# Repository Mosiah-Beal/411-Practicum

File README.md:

# A weather monitor placed near a window
Portland State University Team 4 Practicum Project
Mosiah Beal,	Joshua Dworning,	Andy Nguyen,	Joel Utecht,	Casey McGuire

Uses GNU v3 GENERAL PUBLIC LICENSE

Monitors inputs from DHTxx and Rain sensors, with adjustable tolerances.
Supports Serial communication and has dedicated display/keypad to provide a user interface.
Can be integrated into smart home networks through use of Sinric Pro
Features status leds and piezo buzzer as redundant systems in advent of device failure

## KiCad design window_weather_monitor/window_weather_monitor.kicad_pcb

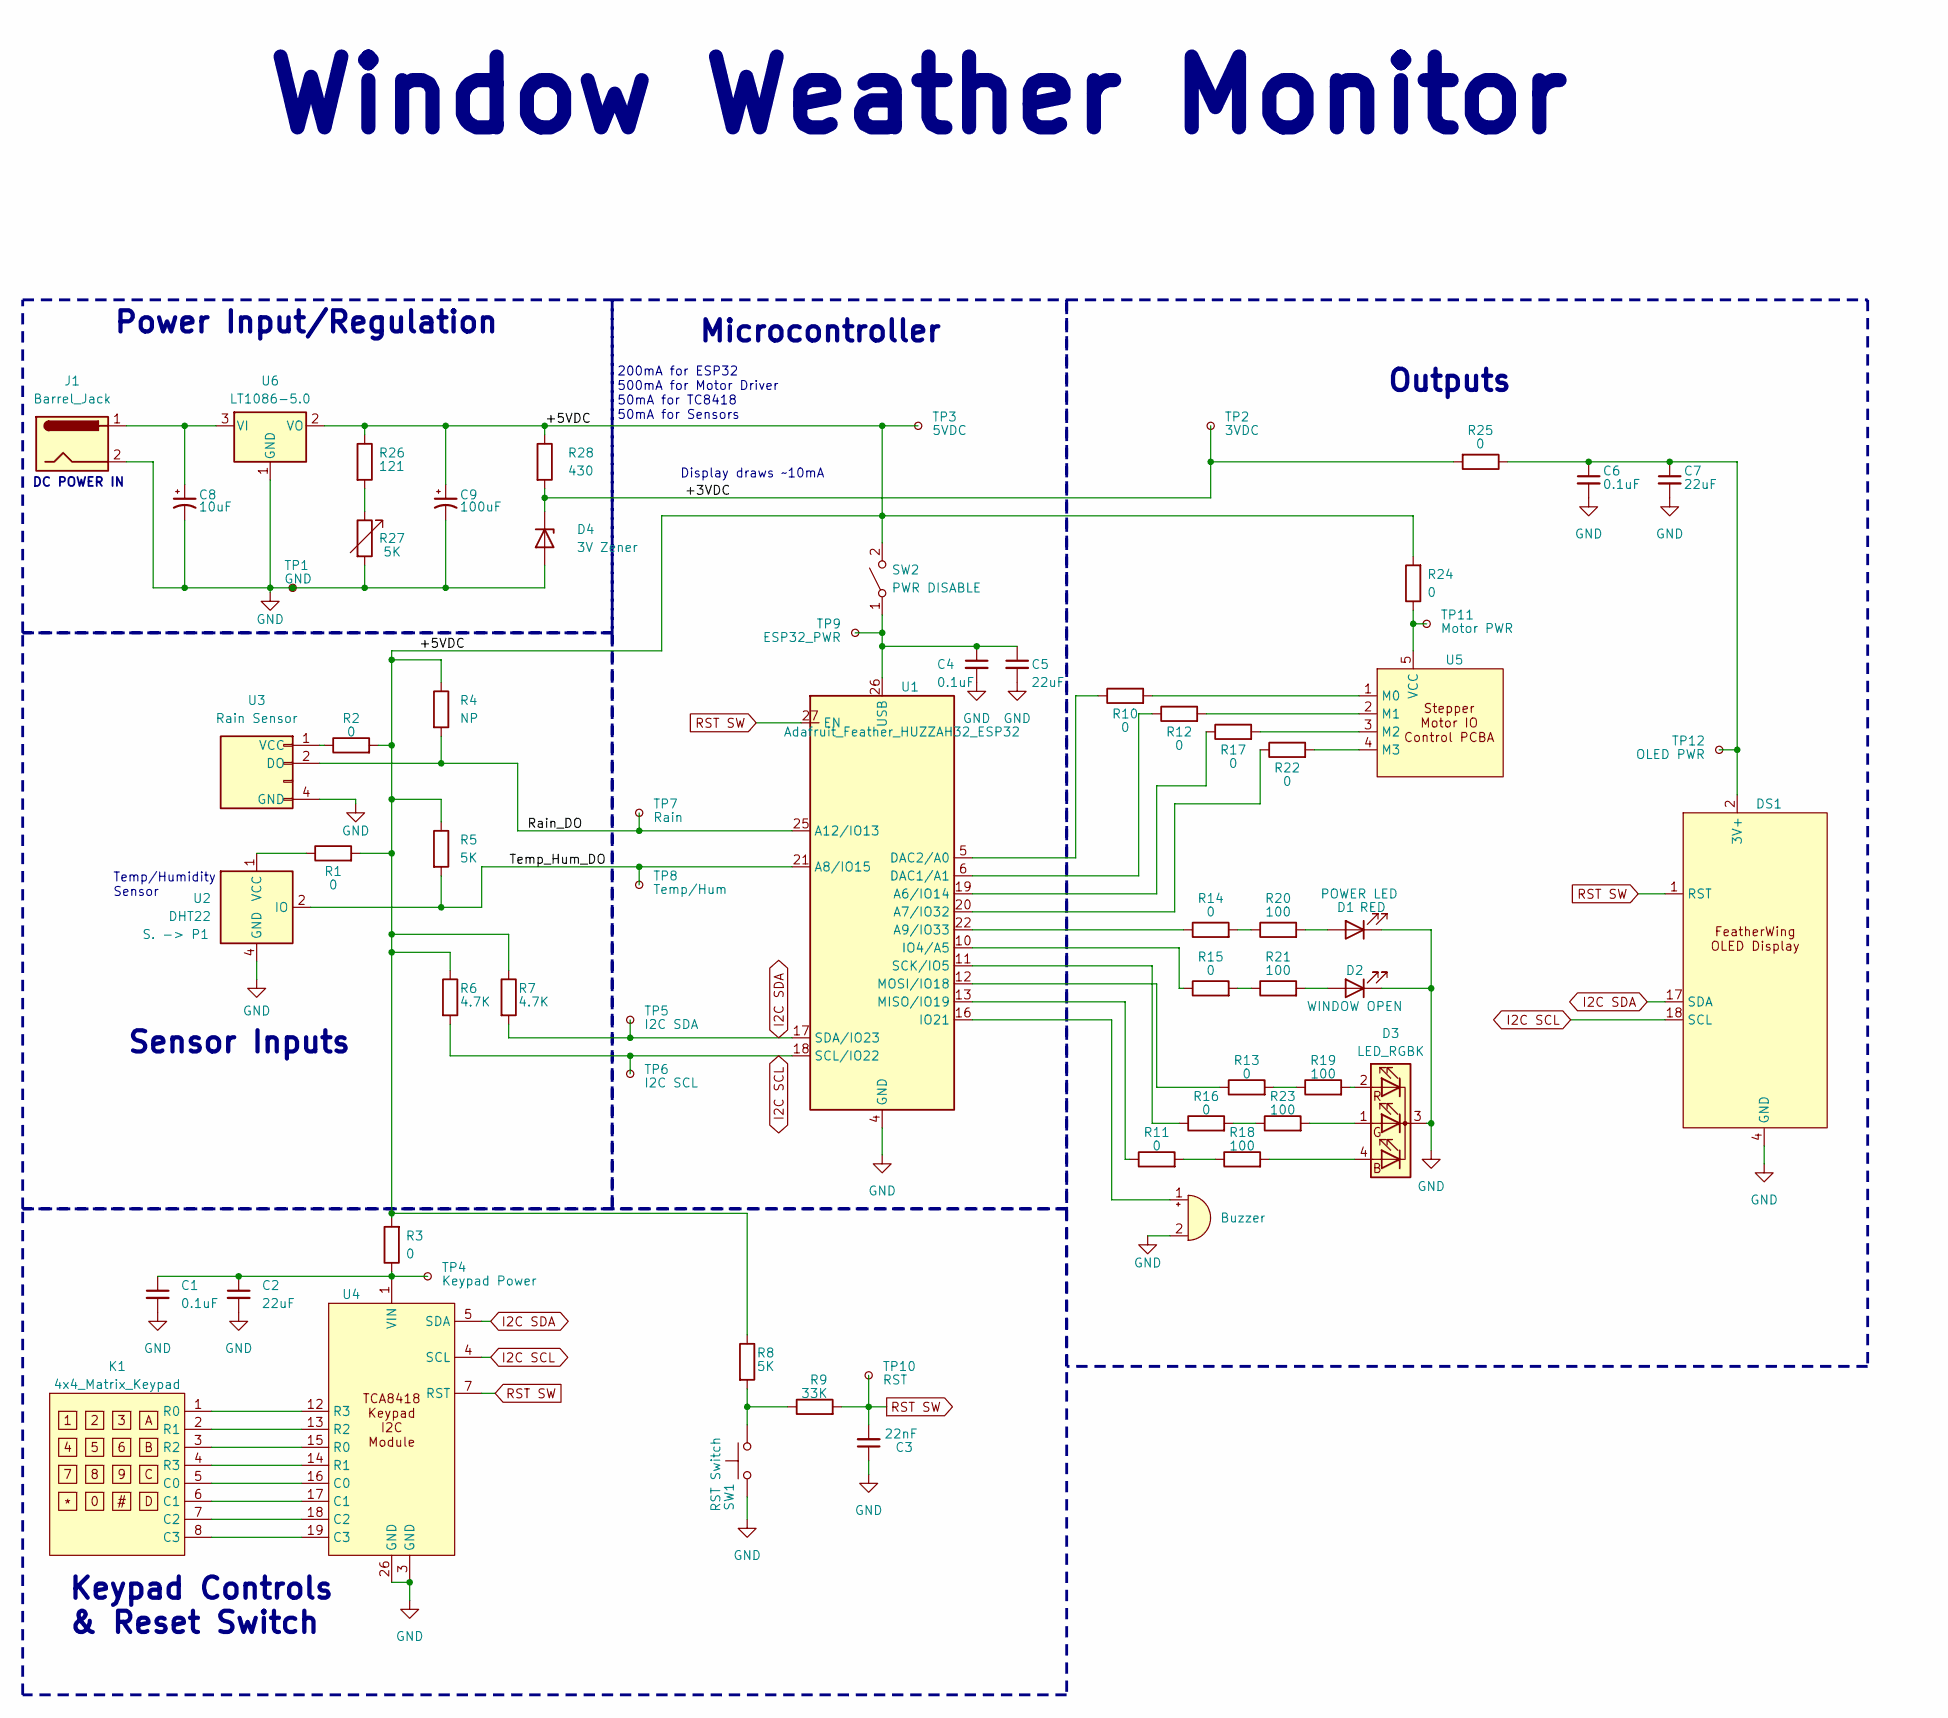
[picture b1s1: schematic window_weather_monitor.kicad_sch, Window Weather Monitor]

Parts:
BZ1: Buzzer; Molex_KK-254_AE-6410-02A_1x02_P2.54mm_Vertical; MFG PN N/A
C1, C4, C6: 0.1uF; C_0603_1608Metric; MFG PN C0603C104K8RAC7867
C2, C5, C7: 22uF; C_1210_3225Metric; MFG PN CL32B226KPJVPNE
C3: 22nF; C_0603_1608Metric; MFG PN CL05B223KP5NNNC
C8: 10uF; CP_Elec_4x5.4; MFG PN EEE-HA1A101WP
C9: 100uF; C_Elec_6.3x5.8; MFG PN EEE-1CA100SR
D1: POWER LED; LED_D5.0mm; MFG PN MT4118-HR-A
D2: WINDOW OPEN; LED_D5.0mm; MFG PN MT2118-G-A
D3: LED_RGBK; LED_D5.0mm-4_RGB; MFG PN HV-5RGB60
D4: 3V Zener; D_SOD-123; MFG PN MMSZ4684-TP
DS1: Adafruit_Feather; MFG PN 128x4 OLED
J1: Barrel_Jack; BarrelJack_CUI_PJ-063AH_Horizontal; MFG PN PJ-063AH
K1: 4x4_Matrix_Keypad
R1, R2, R3, R10, R11, R12, R13, R14, R15, R16, R17, R22, R24, R25: 0; R_0603_1608Metric_Pad0.98x0.95mm_HandSolder; MFG PN RMCF0603ZT0R00
R4: NP; R_0603_1608Metric_Pad0.98x0.95mm_HandSolder; MFG PN RMCF0603ZT0R00
R5, R8: 5K; R_0603_1608Metric_Pad0.98x0.95mm_HandSolder; MFG PN RT0603BRE075KL
R6, R7: 4.7K; R_0603_1608Metric_Pad0.98x0.95mm_HandSolder; MFG PN RK73B1JTTD472J
R9: 33K; R_0603_1608Metric_Pad0.98x0.95mm_HandSolder; MFG PN RMCF0603FT33K0
R18, R19, R20, R21, R23: 100; R_0603_1608Metric_Pad0.98x0.95mm_HandSolder; MFG PN RMCF0603FT100R
R26: 121; R_0603_1608Metric_Pad0.98x0.95mm_HandSolder; MFG PN RMCF0603FT121R
R27: 5K; 5K Trim Pot; MFG PN 84WR5KLFTR
R28: 430; R_0603_1608Metric_Pad0.98x0.95mm_HandSolder; MFG PN RMCF0603FT430R
SW1: RST Switch; SW_PUSH_6mm; MFG PN DAOKI SPST
SW2: PWR DISABLE; FanPinHeader_1x03_P2.54mm_Vertical; MFG PN TS02CQE
TP1: GND; TestPoint_THTPad_D2.0mm_Drill1.0mm
TP2: 3VDC; TestPoint_THTPad_D2.0mm_Drill1.0mm
TP3: 5VDC; TestPoint_THTPad_D2.0mm_Drill1.0mm
TP4: Keypad Power; TestPoint_THTPad_D2.0mm_Drill1.0mm
TP5: I2C SDA; TestPoint_THTPad_D2.0mm_Drill1.0mm
TP6: I2C SCL; TestPoint_THTPad_D2.0mm_Drill1.0mm
TP7: Rain; TestPoint_THTPad_D2.0mm_Drill1.0mm
TP8: Temp/Hum; TestPoint_THTPad_D2.0mm_Drill1.0mm
TP9: ESP32_PWR; TestPoint_THTPad_D2.0mm_Drill1.0mm
TP10: RST; TestPoint_THTPad_D2.0mm_Drill1.0mm
TP11: Motor PWR; TestPoint_THTPad_D2.0mm_Drill1.0mm
TP12: OLED PWR; TestPoint_THTPad_D2.0mm_Drill1.0mm
U1: Adafruit_Feather_HUZZAH32_ESP32; Adafruit_Feather
U2: DHT22; Aosong_DHT11_5.5x12.0_P2.54mm
U3: Rain Sensor; JST_EH_B4B-EH-A_1x04_P2.50mm_Vertical
U4: TCA8418
U5: PinSocket_1x05_P1.27mm_Vertical
U6: LT1086-5.0; TO-220-3_Vertical; MFG PN LT1086CT#PBF

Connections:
/+3VDC: D4.1 (K), R25.2, R28.2, TP2.1
/+5VDC: C9.1, R1.2, R2.2, R3.2, R4.1, R5.1, R6.1, R7.1, R8.1, R24.2, R26.1, R28.1, SW2.2 (B), TP3.1, U6.2 (VO)
/Rain_DO: R4.2, TP7.1, U1.25 (A12/IO13), U3.2 (DO)
/Temp_Hum_DO: R5.2, TP8.1, U1.21 (A8/IO15), U2.2 (IO)
GND: BZ1.2 (+), C1.2, C2.2, C3.1, C4.2, C5.2, C6.2, C7.2, C8.2, C9.2, D1.1 (K), D2.1 (K), D3.3 (K), D4.2 (A), DS1.4 (GND), J1.2, R27.2, SW1.1, TP1.1, U1.4 (GND), U2.4 (GND), U3.4 (GND), U4.3 (GND), U4.26 (GND), U6.1 (GND)
I2C SCL: DS1.18 (SCL), R6.2, TP6.1, U1.18 (SCL/IO22), U4.4 (SCL)
I2C SDA: DS1.17 (SDA), R7.2, TP5.1, U1.17 (SDA/IO23), U4.5 (SDA)
unnamed: BZ1.1 (-), U1.16 (IO21)
unnamed: D1.2 (A), R20.2
unnamed: D2.2 (A), R21.2
unnamed: D3.4 (BA), R18.2
unnamed: D3.1 (GA), R23.2
unnamed: D3.2 (RA), R19.2
unnamed: C6.1, C7.1, DS1.2 (3V+), R25.1, TP12.1
unnamed: R8.2, R9.1, SW1.2
unnamed: R11.2, R18.1
unnamed: R13.2, R19.1
unnamed: R14.2, R20.1
unnamed: R15.2, R21.1
unnamed: R16.2, R23.1
unnamed: R26.2, R27.1
unnamed: C4.1, C5.1, SW2.1 (A), TP9.1, U1.26 (USB)
unnamed: R17.1, U1.19 (A6/IO14)
unnamed: R22.1, U1.20 (A7/IO32)
unnamed: R14.1, U1.22 (A9/IO33)
unnamed: R12.1, U1.6 (DAC1/A1)
unnamed: R10.1, U1.5 (DAC2/A0)
unnamed: R15.1, U1.10 (IO4/A5)
unnamed: R11.1, U1.13 (MISO/IO19)
unnamed: R13.1, U1.12 (MOSI/IO18)
unnamed: R16.1, U1.11 (SCK/IO5)
unnamed: R1.1, U2.1 (VCC)
unnamed: R2.1, U3.1 (VCC)
unnamed: K1.5 (C0), U4.16 (C0)
unnamed: K1.6 (C1), U4.17 (C1)
unnamed: K1.7 (C2), U4.18 (C2)
unnamed: K1.8 (C3), U4.19 (C3)
unnamed: K1.3 (R2), U4.15 (R0)
unnamed: K1.4 (R3), U4.14 (R1)
unnamed: K1.2 (R1), U4.13 (R2)
unnamed: K1.1 (R0), U4.12 (R3)
unnamed: C1.1, C2.1, R3.1, TP4.1, U4.1 (VIN)
unnamed: R10.2, U5.1 (M0)
unnamed: R12.2, U5.2 (M1)
unnamed: R17.2, U5.3 (M2)
unnamed: R22.2, U5.4 (M3)
unnamed: R24.1, TP11.1, U5.5 (VCC)
unnamed: C8.1, J1.1, U6.3 (VI)
RST SW: C3.2, DS1.1 (RST), R9.2, TP10.1, U1.27 (EN), U4.7 (RST), U4.9 (R6)

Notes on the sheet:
Keypad Controls & Reset Switch
200mA for ESP32 500mA for Motor Driver 50mA for TC8418 50mA for Sensors
Display draws ~10mA
Microcontroller
Temp/Humidity Sensor
DC POWER IN
Sensor Inputs
Power Input/Regulation
Outputs
Window Weather Monitor

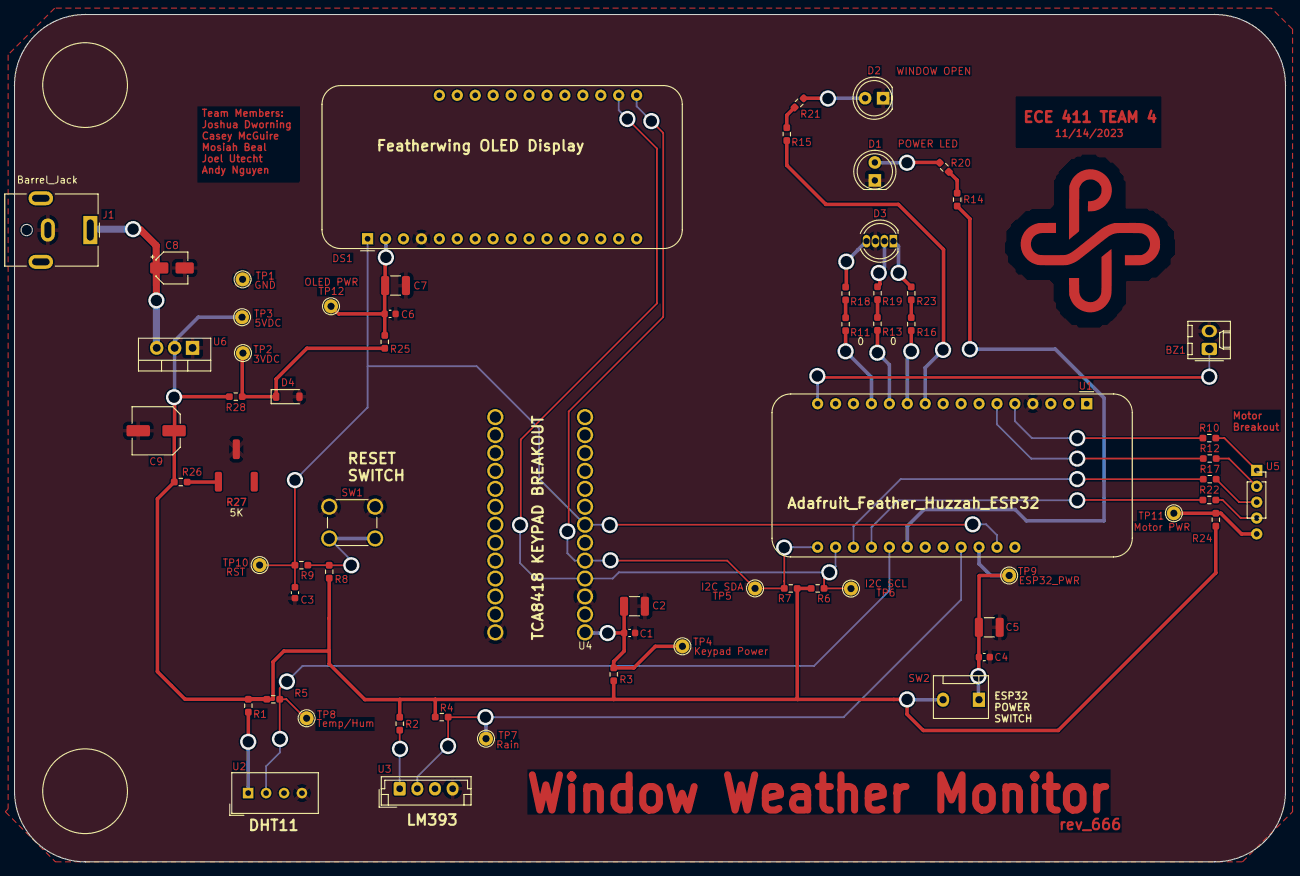
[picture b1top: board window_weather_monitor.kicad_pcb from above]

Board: 2 copper layers, 180.0 x 120.0 mm, 65 parts (0 on the bottom side), 41 nets.

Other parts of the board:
Ref**: Val**; PSU_F.Cu

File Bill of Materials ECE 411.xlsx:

Bill Of Materials for: [TEAM 4] [Window Weather Monitor]
Last modified: [11/8/23]
PCB version: [PCB VERSION #1]
BOM revision: [BOM REVISION #1] |  |  |  | P/NP | = Place/Not Place (components marked NP are not stuffed on the board)
Item | Qty | Part References | Value | P/NP | Mfg | Mfg PN | Description | Dist | Dist Part Number | Cost Ea. | Cost Total | Received (Y/N) | Received QTY
1 | 1 | BZ1 |  | P | Mallory Sonalert | AST1341MCTRQ | BUZZER PIEZO 5V 13X13MM SMD | Digi-Key | 458-AST1341MCTRQCT-ND | 2.06 | 2.06 | Y | 3
2 | 3 | C1, C4, C6 | 0.1uF | P | Kemet | C0603C104K8RAC7867 | CAP CER 0.1UF 10V X7R 0603 | Digi-Key | 399-C0603C104K8RAC7867TR-ND | 0.1 | 0.2 | N
3 | 3 | C2, C5, C7 | 22uF | P | Samsung | CL32B226KPJVPNE | CAP CER 22UF 10V X7R 1210 | Digi-Key | 1276-CL32B226KPJVPNETR-ND | 0.74 | 2.2199999999999998 | N
4 | 1 | C3 | 0.022uF | P | Wurth Elektronik | 885012206016 | CAP CER 0.022UF 10V X7R 0603 | Digi-Key | 732-7935-2-ND | 0.1 | 0.4 | N
5 | 1 | C8 | 100UF | P | Panasonic | EEE-HA1A101WP | CAP ALUM 100UF 10V | Digi-Key | PCE4169TR-ND | 0.42 | 2.1 | N | 0
6 | 1 | C9 | 10UF | P | Panasonic | EEE-1CA100SR | CAP ALUM 10UF 16V | Digi-Key | PCE3878TR-ND | 0.32 | 1.92 | N
7 | 1 | D1 | RED | P | Marktech Optoelectronics | MT4118-HR-A | 5MM LED RED DIFFUSED | Digi-Key | 1125-1188-ND | 0.32 | 0.32 | Y | 3
8 | 1 | D2 | GREEN | P | Marktech Optoelectronics | MT2118-G-A | 5MM LED GREEN DIFFUSED | Digi-Key | 1125-1184-ND | 0.31 | 0.31 | Y | 3
9 | 1 | D3 | RGBK | P | Inolux | HV-5RGB60 | 5MM LED RGBK DIFFUSED | Digi-Key | 1830-1014-ND | 1 | 1 | Y | 2
10 | 1 | D4 | 3V | P | Micro Commercial Co | MMSZ4684-TP | DIODE ZENER 3.3V 500MW SOD123 | Digi-Key | MMSZ4684-TPMSTR-ND | 0.12 | 0.12 | N
11 | 1 | DS1 |  | P | Adafruit | 128x4 OLED | OLED DISPLAY | Adafruit | 2900 | 14.95 | 14.95 | Y | 3
12 | 1 | J1 |  | P | CUI Devices | PJ-063AH | CONN PWR BARREL JACK | Digi-Key | CP-063AH-ND | 1.55 | 1.55 | Y | 5
13 | 1 | K1 |  | P | Parallax | 4X4MEMKYPD | 4X4 MEMBRANE KEYPAD | Parallax | 27899 | 9.9499999999999993 | 9.9499999999999993 | Y | 2
14 | 14 | R1, R2, R3, R10, R11, R12, R13, R14, R15, R16, R17, R22, R24, R25 | 0 Ohm | P | Stackpole Elec. Inc. | RMCF0603ZT0R00 | RES 0 OHM JUMPER 1/10W 0603 | Digi-Key | RMCF0603ZT0R00TR-ND | 0.1 | 1.4000000000000001 | N
15 | 1 | R4 | 5K Ohm | NP | Yageo | RT0603BRE075KL | RES 5K OHM 1/10W 0603 | Digi-Key | 13-RT0603BRE075KLTR-ND | 0.39 | 0.39 | N
16 | 2 | R5, R8 | 5K Ohm | P | Yageo | RT0603BRE075KL | RES 5K OHM 1/10W 0603 | Digi-Key | 13-RT0603BRE075KLTR-ND | 0.39 | 0.78 | N
17 | 2 | R6, R7 | 4.7 kOhm | P | KOA Speer Electronics | RK73B1JTTD472J | RES 4.7K OHM 1/10W 0603 | Digi-Key | 2019-RK73B1JTTD472JTR-ND | 0.1 | 0.2 | N
18 | 1 | R9 | 33 kOhm | P | Stackpole Elec. Inc. | RMCF0603FT33K0 | RES 33K OHM 1/10W 0603 | Digi-Key | RMCF0603FT33K0TR-ND | 0.1 | 0.1 | N
19 | 5 | R18, R19, R20, R21, R23 | 100 Ohm | P | Stackpole Elec. Inc. | RMCF0603FT100R | RES 100 OHM 1/10W 0603 | Digi-Key | RMCF0603FT100RTR-ND | 0.1 | 0.5 | N
20 | 1 | R26 | 121 Ohm | P | Stackpole Elec. Inc. | RMCF0603FT121R | RES 121 OHM 1/10W 0603 | Digi-Key | RMCF0603FT121RTR-ND | 0.1 | 0.1 | N
21 | 1 | R27 | 5 kOHM | P | TT Electronics | 84WR5KLFTR | TRIMMER 5K OHM 0.25W SMD | Digi-Key | 987-1810-2-ND | 3.36 | 3.36 | N
22 | 1 | R28 | 430 Ohm | P | Stackpole Elec. Inc. | RMCF0603FT430R | RES 430 OHM 1/10W 0603 | Digi-Key | RMCF0603FT430RTR-ND | 0.1 | 0.1 | N
23 | 1 | SW1 |  | P | DAOKI | SPST THT SW | 6MM MOMENTARY SWITCH THT | Amazon | DAOKITHTPB | 0.05 | 0.05 | Y | 5
24 | 1 | SW2 |  | P | C&K | TS02CQE | SWITCH SLIDE SPST 1A 120V | Digi-Key | CKN10666-ND | 7.76 | 7.76 | Y | 100
25 | 1 | U1 |  | P | Adafruit | ESP32-HUZZAH | Adafruit ESP32 Huzzah Feather Board | Adafruit | 3405 | 19.95 | 19.95 | Y | 2
26 | 1 | U2 |  | P | Adafruit | DHT22 | TEMP/HUM SENSOR | Adafruit | 385 | 9.9499999999999993 | 9.9499999999999993 | Y | 2
27 | 1 | U3 |  | P | HiLetgo | LM393 | LM393 MOISTURE SENSOR | Amazon | HILETGO-LM393 | 2.2000000000000002 | 2.2000000000000002 | Y | 4
28 | 1 | U4 |  | P | Adafruit | TCA8418 | KEYPAD EXANDER BREAKOUT | Adafruit | 4918 | 5.95 | 5.95 | Y | 3
29 | 1 | U5 |  | P | ULN | ULN2003 | STEPPER MOTOR DRIVE BREAKOUT | Amazon | ULN2003 | 2.2999999999999998 | 2.2999999999999998 | Y | 1
30 | 1 | U6 |  | P | Analog Devices | LT1086CT#PBF | IC REG LIN POS ADJ 1.5A TO220-3 | Digi-Key | 505-LT1086CT#PBF-ND | 6.29 | 6.29 | Y | 5
 |  |  |  |  |  |  |  |  |  | TOTAL: | 98.480000000000018
VERSION INFO
Rev |  | Date |  | Notes
1.0r0 |  | 45237 |  | Initial BOM. Not everything chosen but mostly there.
2.0r0 |  | 45243 |  | Updated BOM. Almost everything chosen.
2.0r1 |  | 45252 |  | Updated BOM to add part values where applicable. Also added received section.

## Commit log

2023-10-12 Added 411 Practicum Project Planning.drawio.pdf
2023-10-12 Added Zoomed_out_Tree.drawio.png
2023-10-17 Add files via upload
    Adding second draft of requirements made during meeting on Oct. 17, 2023
2023-10-17 Add files via upload
    Uploading rough draft of system architecture
2023-10-17 Added System Architecture-Page-2.drawio.png
2023-10-17 Added System Architecture-Page-1.drawio.png
2023-10-19 Create Folder Creation
2023-10-19 Initial file upload
2023-10-19 Added PDS
2023-10-26 Preliminary Schematic
2023-10-26 Preliminary Schematic
    Updated schematic
2023-10-26 Moving files into planning documents folder
2023-10-26 Uploading first major test of Temp sensor
2023-10-26 Updating DHT11 Sketch
    Added debugging print statements and reset timer on 'same value' conditional branch
2023-10-26 Initial photos of breadboard prototype
    Woooo software oriented projects are easy to draft/prototype
2023-11-06 Add files via upload
    This arduino sketch alternates between clockwise and counterclockwise rotation of the stepper motor without using the delay function.
2023-11-06 Uploading PCBA Project File
    This is an updated schematic and includes all of the IO that we have settled on. The layout should be completed within the next couple days. I may also add a few capacitors as needed.
2023-11-08 Moved arduino files into a zip
2023-11-08 Refactored Arduino code using VSC (Visual Studio Code) and included Sinric Pro zip library
2023-11-08 Unzipping files so you can navigate them in Github
2023-11-08 Kicad Project Files
    .zip archive of the Kicad project files.
2023-11-08 Updated Kicad Project Files
2023-11-08 Added BOM
2023-11-08 Add files via upload
    11/8/23 Meeting notes
2023-11-09 BOM Done.
2023-11-09 Updating Folders and Adding New Schematics/Layout
2023-11-09 Added Level0_Diagram.drawio.png
2023-11-09 Added Level1_Diagram.drawio.png
2023-11-09 Moved old dwgs to Archive, updated schematic/layout pdf
2023-11-09 Removed Duplicate Files
2023-11-10 Add files via upload
    Updated to reflect the material shown in Lecture 6 regarding functional decomposition
2023-11-10 Updated BOM
2023-11-11 Updated Schematic and PCBA Layout
    This may be our final layout unless we upgrade the power supply.
2023-11-11 Last Update Layout
    Updated Schematic/Layout/BOM/Project Archive
2023-11-11 Here's a fun picture of the PCB
2023-11-11 Slight change to footprints on PCB.
    Not going to change the pdf for now. This is only critical for fab.
2023-11-12 Update to Schematic and Layout
    Added new VReg circuit
2023-11-13 Updating BOM and Project File
    Project File update renames A1 to U1
2023-11-13 Updated Schematic and PCBA
    Barrel Jack was in odd placement on board.
2023-11-13 Update Bill of Materials ECE 411.xlsx
    Updated BOM to latest values
2023-11-13 Updated PCBA
    Now with more silkscreen!
    I swear I'm done updating this, for now.
2023-11-14 Unzipped Kicad project file
    I did this to make the files more accessible on Git
2023-11-14 Schematic Update
    It's another schematic update!!
    Removed quotes around title blocks
    Reprinted schematic and combined pdfs
2023-11-15 Updated PCB
    Updated the schematic, layout, generated gerber files for fab, added requisite info on PCB.
2023-11-15 Updated name of file for OSHPark upload
2023-11-16 Update ece411-t04-window-weather-monitor-pcb.zip
    Final update before upload to fab. Small changes after DRC check revealed some nets were off.
2023-11-16 Receipt for PCBA from OSHPark
2023-11-16 Saving progress on updating function calls to work with recently chosen/updated components and added initial program description
2023-11-16 I am learning how to push
2023-11-16 Helped Casey with the installation of files, found that he needed some dependencies that were not tracked in initial pass.
2023-11-17 Updated Library folder and made further progress on Monitor code. Added a state structure and some stub test functions
2023-11-17 Added menu structures, still need to implement the functionality of choosing an option
2023-11-20 Uploading 2D and 3D layouts
2023-11-22 Implemented Menu functionality, needs testing but does compile
2023-11-23 Update Bill of Materials ECE 411.xlsx
    added received/received qty/value columns to BOM. Updated to parts we have at Josh's house.
2023-11-23 Step 1 of menu working. Can scroll up and down main menu. Can't descend (or ascend?) yet.
2023-11-23 I found the bug. I deleted the menu passed into select option. instead of checking if menu == NULL, i was setting menu = NULL. (Killing the subsequent code)
2023-11-23 Final commit for tonight. Needs help going back up menu. Needs to wait until user enters value when changing settings, needs more function definitions.
2023-11-23 Update to BOM
    updated if parts were received
2023-11-29 Create .gitignore
    Added a .gitignore file to reduce commit changes where unneeded
2023-11-30 Updated Testing functions, added more info, moved pin declarations to own section
2023-12-01 Working menu, Can update user settings, Found issues with pinouts
2023-12-01 Changes to make a working board
2023-12-01 Update folder
2023-12-02 Working Keypad menu, I2C display doesn't seem to be working. (Initializes, but no visual output)
2023-12-03 Add files via upload
    Incomplete obviously, but a good start. Will iron out redundancies and fill in other requirements before the presentation on Friday, 12/8/23.
2023-12-05 Resolved OLED display issue, was using the SH librarby when I should have been using the SSD library.
2023-12-05 Printing menu on I2C, currently goes offscreen
2023-12-05 Working menu navigation over I2C (Serial input), need to add print messages telling the user what to do (over I2C).
2023-12-06 Adjusted some menu strings, added software reset functionality, modified draw graph(still needs work) added more prototypes & TODO items
2023-12-06 Moved the menu out of the main file and into a header file + cpp. Functionality remains the same, just relocated inside a library.
2023-12-06 Recording TODO for tomorrow
2023-12-07 Added more todo
2023-12-07 Storing work (will return if previous revision works)
2023-12-07 Pushing before major rewrite
2023-12-08 Can exit out of monitor state, need to add back in the settings user messages
2023-12-08 Added file for overview
2023-12-08 Demo????
2023-12-08 Quick overview for Demo Presentation
2023-12-08 Renamed printMenu to printOLEDMenu
2023-12-08 Updated flags, added shutdown stub
2023-12-08 Flow Diagram
2023-12-08 Demo Update
2023-12-11 Final updates to Schematic/Layout for EPL refab.
2024-01-22 Added ECE485_HW1_Transition_Diagram.png
2024-01-22 Delete Planning Documents/ECE485_HW1_Transition_Diagram.png
    Wrong place
